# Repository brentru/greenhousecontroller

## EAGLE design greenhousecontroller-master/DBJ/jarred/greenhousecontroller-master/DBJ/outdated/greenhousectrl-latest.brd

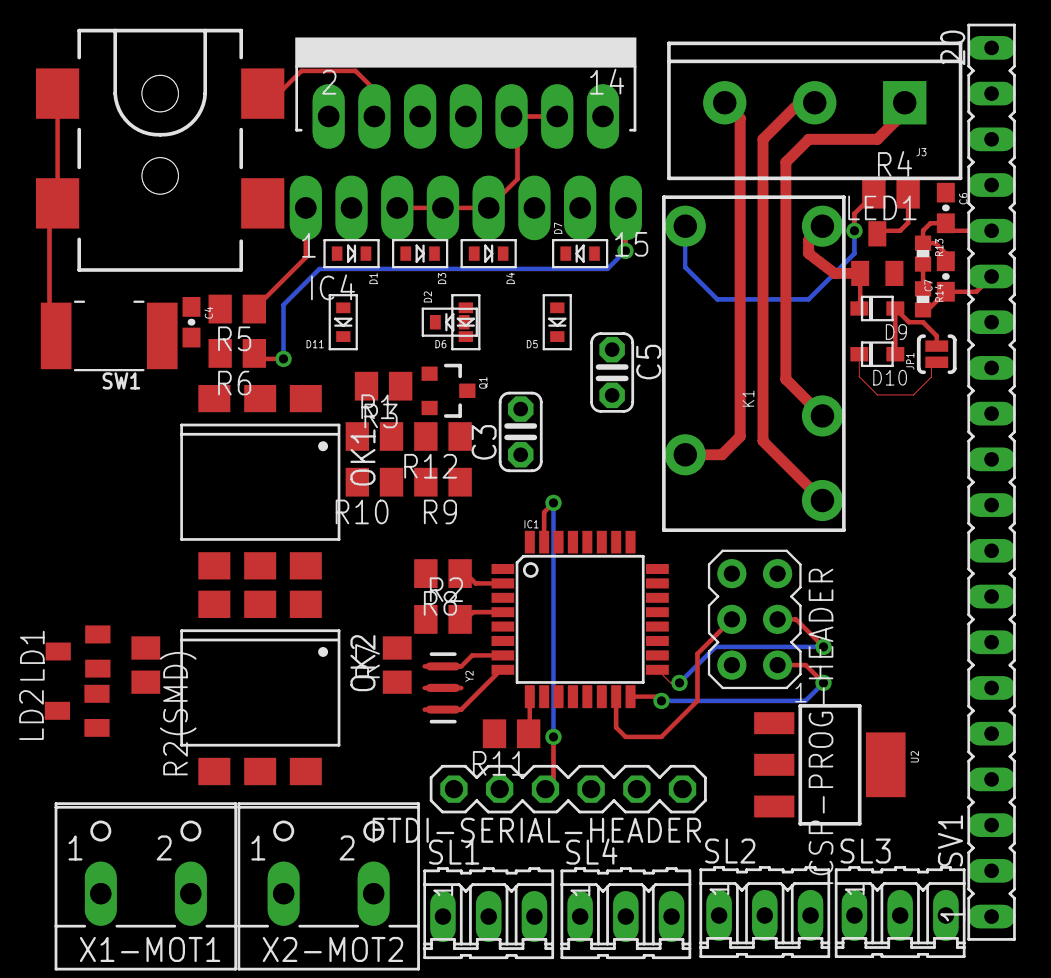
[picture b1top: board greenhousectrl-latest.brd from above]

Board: 2 copper layers, 54 parts (0 on the bottom side), 44 nets.

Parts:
C3, C5: C025-024X044
C4, C6, C7: 0.1uF; 0603-CAP
D1, D2, D3, D4, D5, D6, D7, D11: SOD-523
D9: 1N4148; SOD-323F
D10: Zener; SOD-323F
FTDI-SERIAL-HEADER: HEADER-06X1-MALE; 06X1-PTH
IC1: ATMEGA168TQFP-08; TQFP32-08
IC4: L298; MULTIWATT-15
ICSP-PROG-HEADER: AVRISP-6; AVRISP
J1: 5.5x2.1mm Barrel; POWER_JACK_SMD
J3: SCREWTERMINAL-5MM-3
JP1: JUMPER-PAD-2-NOYES_SILK; PAD-JUMPER-2-NO_YES_SILK
K1: RELAYPTH4; RELAY-JZC
LD1, LD2: PL006-WCR12; SOT23
LED1: PL006-WCR13; SOT23
OK1, OK2: 4N27SM; DIL6-SMD
Q1: MMBT2222A; SOT23-3
R1, R2, R2(SMD), R5, R6, R7, R8, R9, R10, R11, R12: M0805
R3, R4: 1K; M0805
R13, R14: 0402-RES
SL1, SL2, SL3, SL4: 03P
SV1: FE20
SW1: BTN_CK_KSS
U2: V_REG_317SMD; SOT223
X1-MOT1, X2-MOT2: W237-102
Y2: 16MHZ; RESONATOR-SMD

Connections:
+5V: C3.1, C7.1, FTDI-SERIAL-HEADER.3, IC1.4, IC1.6, IC1.18, IC4.5, IC4.7, IC4.9, IC4.10, IC4.12, ICSP-PROG-HEADER.2, R2.1, R2(SMD).2, R14.2, SL1.2, SL2.2, SL3.2, SL4.2, SV1.2, SV1.15, U2.2
+12V: C5.1, C6.1, D1.K, D3.K, D5.K, D7.K, IC4.4, J1.VIN0, U2.3
COIL: D10.C, JP1.1, K1.1, Q1.3, R4.1
COMMON: J3.3, K1.4
DIODENODE: D9.A, D10.A, JP1.2
DTR: C4.1, FTDI-SERIAL-HEADER.6
ENA: IC4.6, OK2.5
ENB: IC4.11, OK1.5
GND: C3.2, C5.2, C6.2, C7.2, D2.A, D4.A, D6.A, D11.A, FTDI-SERIAL-HEADER.1, IC1.3, IC1.5, IC1.21, IC4.8, ICSP-PROG-HEADER.6, J1.GND, J1.P$4, LD1.3, LD2.3, OK1.6, OK2.6, Q1.2, R5.2, R6.2, R7.1, R9.1, R10.1, R12.1, R13.1, SL1.1, SL2.1, SL3.1, SL4.1, SV1.1, SV1.3, SV1.16, SW1.P$2, Y2.2
MISO: IC1.16, ICSP-PROG-HEADER.1, SV1.13
MOSI: IC1.15, ICSP-PROG-HEADER.4, SV1.12
unnamed: OK2.1, R8.2
unnamed: LD2.1, R2.2
unnamed: LED1.3, R4.2
unnamed: OK2.2, R7.2
unnamed: OK2.4, R9.2
unnamed: Q1.1, R3.1
unnamed: R13.2, R14.1, U2.1
unnamed: OK1.1, R11.2
unnamed: OK1.2, R10.2
unnamed: LD1.1, R1.1
unnamed: IC1.7, Y2.1
unnamed: OK1.4, R12.2
unnamed: IC1.8, Y2.3
NC: J3.1, K1.2
NO: J3.2, K1.3
OUT1: D1.A, D11.K, IC4.2, X1-MOT1.1
OUT2: D2.K, D3.A, IC4.3, X1-MOT1.2
OUT3: D4.K, D5.A, IC4.13, X2-MOT2.1
OUT4: D6.K, D7.A, IC4.14, X2-MOT2.2
PB0: IC1.12, R3.2
PC0: IC1.23, SL1.3
PC1: IC1.24, SL2.3
PC2: IC1.25, SL3.3
PC3: IC1.26, SL4.3
PD4: IC1.2, R8.1
PD5: IC1.9, R11.1
RST: C4.2, IC1.29, ICSP-PROG-HEADER.5, R2(SMD).1, SW1.P$1
RX: FTDI-SERIAL-HEADER.5, IC1.30
SCK: IC1.17, ICSP-PROG-HEADER.3, R1.2, SV1.14
SEN_A: IC4.1, R5.1
SEN_B: IC4.15, R6.1
TX: FTDI-SERIAL-HEADER.4, IC1.31
VCC: D9.C, K1.5, LED1.1

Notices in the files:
parts and their libraries:
SparkFun-Capacitors: Licensing: Creative Commons ShareAlike 4.0 International - https://creativecommons.org/licenses/by-sa/4.0
